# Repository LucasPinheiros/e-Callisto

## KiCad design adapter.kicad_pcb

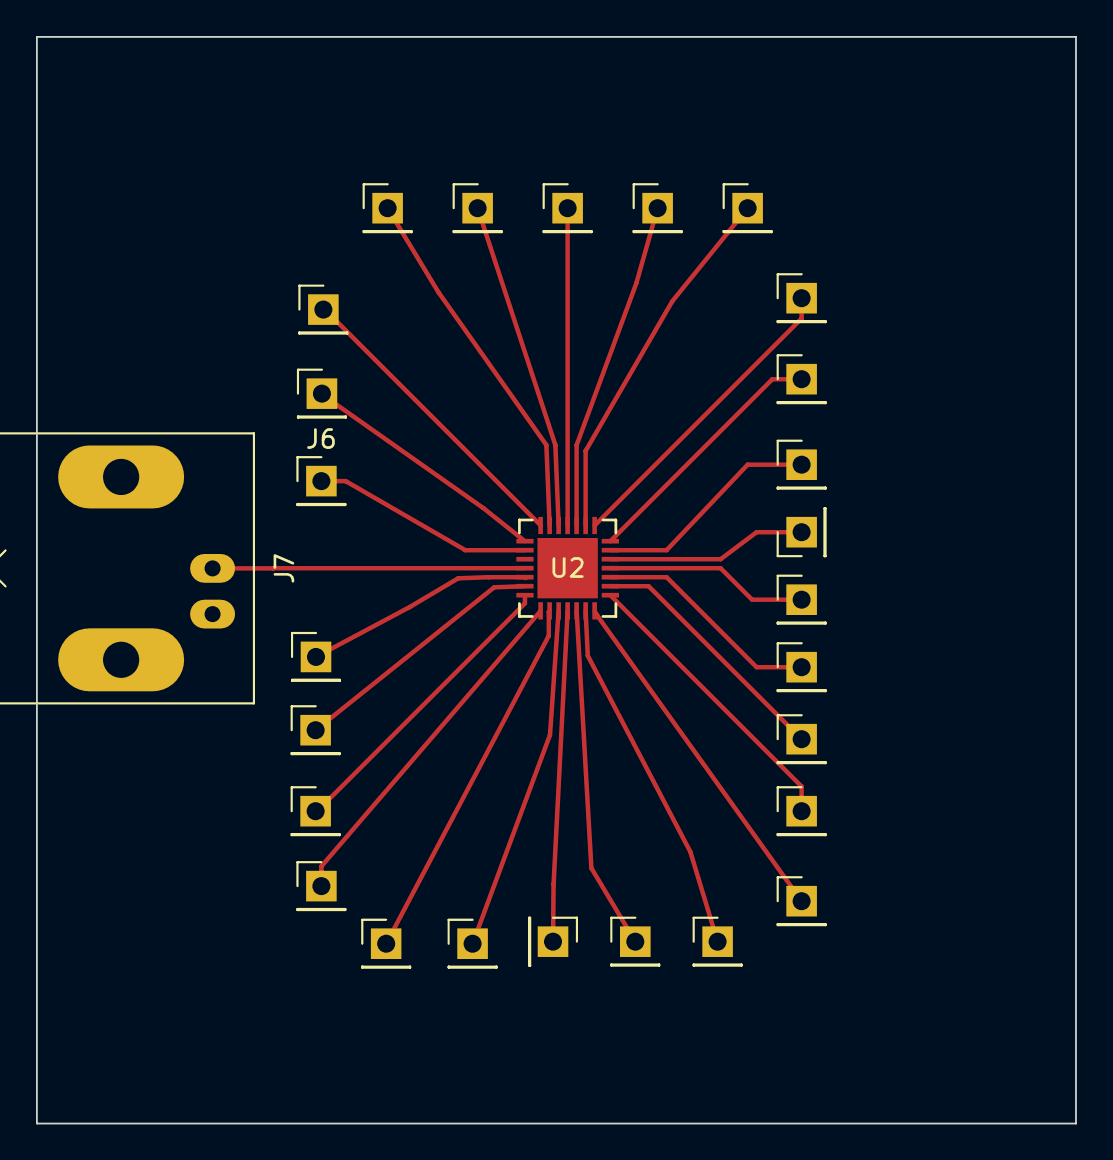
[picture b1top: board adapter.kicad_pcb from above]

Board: 2 copper layers, 57.7 x 60.4 mm, 28 parts (0 on the bottom side), 27 nets.

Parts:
J1, J2, J3, J4, J5, J6, J8, J9, J10, J11, J12, J13, J14, J15, J16, J17, J18, J19, J20, J21, J22, J23, J24, J25, J26, J27: Conn_01x01_Pin; PinHeader_1x01_P2.54mm_Vertical
J7: Conn_01x01_Pin; BNC_Amphenol_B6252HB-NPP3G-50_Horizontal
U2: MAX2121ETI+; MAX2121ETI&plus_

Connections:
unnamed: J1.1, U2.1 (VCC_RF2)
unnamed: J2.1, U2.20 (IOUT-)
unnamed: J3.1, U2.19 (IOUT+)
unnamed: J4.1, U2.18 (QOUT-)
unnamed: J5.1, U2.17 (QOUT+)
unnamed: J6.1, U2.2 (VCC_RF1)
unnamed: J7.1, U2.4 (RFIN)
unnamed: J8.1, U2.5 (GC1)
unnamed: J9.1, U2.6 (VCC_LO)
unnamed: J10.1, U2.7 (VCC_VCO)
unnamed: J11.1, U2.8 (BYPVCO)
unnamed: J12.1, U2.9 (TUNEVCO)
unnamed: J13.1, U2.10 (GNDTUNE)
unnamed: J14.1, U2.12 (CPOUT)
unnamed: J15.1, U2.13 (VCC_SYN)
unnamed: J16.1, U2.14 (XTAL)
unnamed: J17.1, U2.11 (GNDSYN)
unnamed: J18.1, U2.16 (VCC_DIG)
unnamed: J19.1, U2.15 (REFOUT)
unnamed: J20.1, U2.28 (ADDR)
unnamed: J21.1, U2.27 (SCL)
unnamed: J22.1, U2.26 (SDA)
unnamed: J23.1, U2.25 (VCC_BB)
unnamed: J24.1, U2.24 (QDC-)
unnamed: J25.1, U2.23 (QDC+)
unnamed: J26.1, U2.22 (IDC-)
unnamed: J27.1, U2.21 (IDC+)

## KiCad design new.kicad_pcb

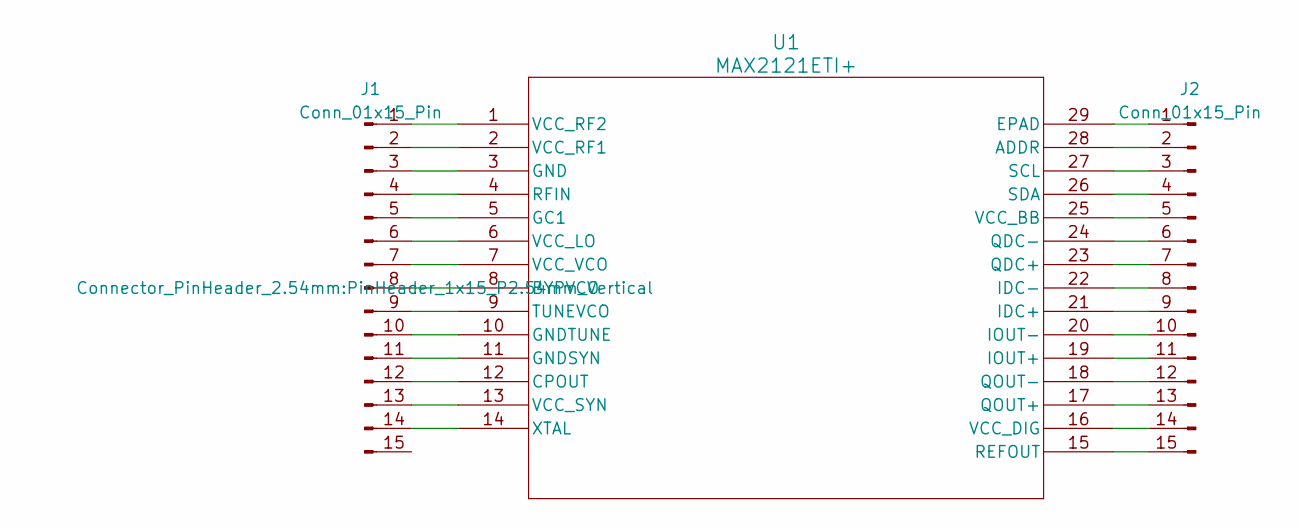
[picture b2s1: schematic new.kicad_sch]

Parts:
J1, J2: Conn_01x15_Pin; PinHeader_1x15_P2.54mm_Vertical
U1: MAX2121ETI+; 21-0140L_T2855-3_MXM

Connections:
unnamed: J1.1, U1.1 (VCC_RF2)
unnamed: J1.2, U1.2 (VCC_RF1)
unnamed: J1.3, U1.3 (GND)
unnamed: J1.4, U1.4 (RFIN)
unnamed: J1.5, U1.5 (GC1)
unnamed: J1.6, U1.6 (VCC_LO)
unnamed: J1.7, U1.7 (VCC_VCO)
unnamed: J1.8, U1.8 (BYPVCO)
unnamed: J1.9, U1.9 (TUNEVCO)
unnamed: J1.10, U1.10 (GNDTUNE)
unnamed: J1.11, U1.11 (GNDSYN)
unnamed: J1.12, U1.12 (CPOUT)
unnamed: J1.13, U1.13 (VCC_SYN)
unnamed: J1.14, U1.14 (XTAL)
unnamed: J2.1, U1.29 (EPAD)
unnamed: J2.2, U1.28 (ADDR)
unnamed: J2.3, U1.27 (SCL)
unnamed: J2.4, U1.26 (SDA)
unnamed: J2.5, U1.25 (VCC_BB)
unnamed: J2.6, U1.24 (QDC-)
unnamed: J2.7, U1.23 (QDC+)
unnamed: J2.8, U1.22 (IDC-)
unnamed: J2.9, U1.21 (IDC+)
unnamed: J2.10, U1.20 (IOUT-)
unnamed: J2.11, U1.19 (IOUT+)
unnamed: J2.12, U1.18 (QOUT-)
unnamed: J2.13, U1.17 (QOUT+)
unnamed: J2.14, U1.16 (VCC_DIG)
unnamed: J2.15, U1.15 (REFOUT)

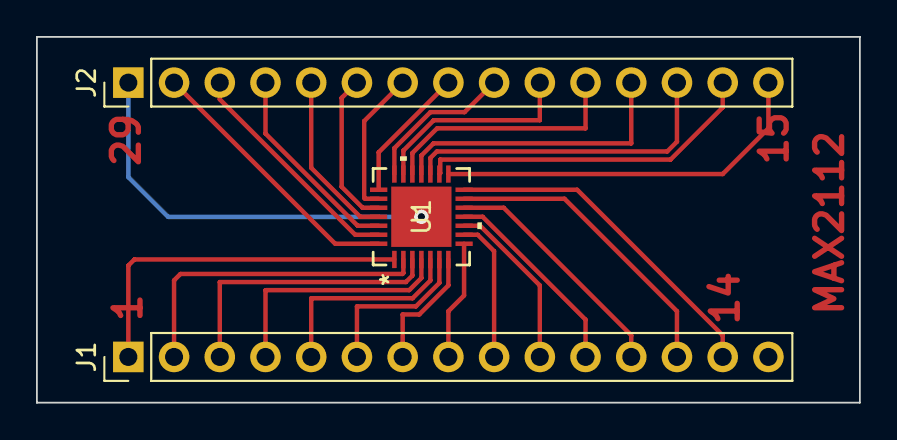
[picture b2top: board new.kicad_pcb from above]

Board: 2 copper layers, 45.7 x 20.3 mm, 3 parts (0 on the bottom side), 29 nets.

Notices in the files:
parts and their libraries:
Copyright 2016 Accelerated Designs. All rights reserved.
